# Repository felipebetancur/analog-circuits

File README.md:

# analog-circuits
Various eagle files for analog synths

# Setup
* Add repo to eagle projects directory list, e.g., $HOME/workspace/analog-circuits
* Clone MTIID eagle library
* Add MTIID eagle library to library directory list, e.g., $HOME/workspace/mtiid-eagle-library

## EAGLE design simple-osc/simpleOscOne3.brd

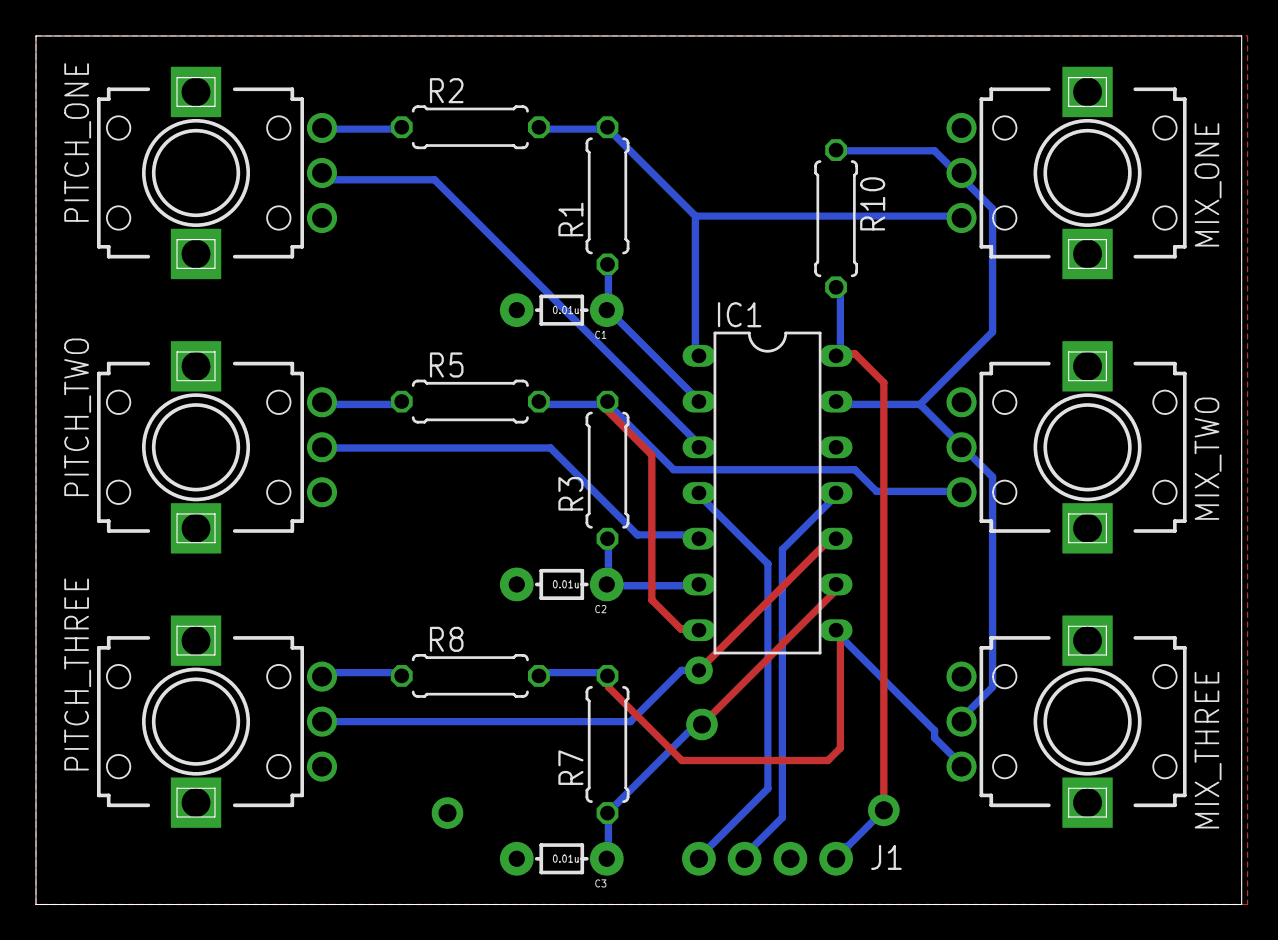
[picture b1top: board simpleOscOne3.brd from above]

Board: 2 copper layers, 67.0 x 48.2 mm, 19 parts (0 on the bottom side), 17 nets.

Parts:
C1, C2, C3: 0.01u; AXIAL-5MM
FRAME1: FRAME-LETTERNO_PACKAGE; DUMMY
IC1: TL084P; DIL14
J1: 1X04_NO_SILK_ALL_ROUND
MIX_ONE: US-EVUF2A; EVUF
MIX_THREE: US-EVUF2A; EVUF
MIX_TWO: US-EVUF2A; EVUF
PITCH_ONE: US-EVUF2A; EVUF
PITCH_THREE: US-EVUF2A; EVUF
PITCH_TWO: US-EVUF2A; EVUF
R1, R2, R3, R5, R7, R8, R10: 10k; 0207/7

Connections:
GND: C1.P$2, C2.P$2, C3.P$2, IC1.12, J1.2, MIX_ONE.1, MIX_THREE.1, MIX_TWO.1, PITCH_ONE.1, PITCH_THREE.1, PITCH_TWO.1
unnamed: PITCH_ONE.3, R2.1
unnamed: IC1.1, MIX_ONE.3, R1.2, R2.2
unnamed: IC1.7, MIX_TWO.3, R3.2, R5.2
unnamed: IC1.3, PITCH_ONE.2
unnamed: C1.P$1, IC1.2, R1.1
unnamed: PITCH_TWO.3, R5.1
unnamed: IC1.5, PITCH_TWO.2
unnamed: C2.P$1, IC1.6, R3.1
unnamed: IC1.8, MIX_THREE.3, R7.2, R8.2
unnamed: PITCH_THREE.3, R8.1
unnamed: IC1.10, PITCH_THREE.2
unnamed: C3.P$1, IC1.9, R7.1
unnamed: IC1.13, MIX_ONE.2, MIX_THREE.2, MIX_TWO.2, R10.1
OUTPUT: IC1.14, J1.1, R10.2
VCC: IC1.4, J1.4
VDD: IC1.11, J1.3

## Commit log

2017-03-09 initial upload of simple oscillator
2017-04-06 creating dir structure for oscillators and sequential circuits
2017-04-06 renaming simple-osc to relaxation-oscillator
2017-04-06 added falstad gif of relaxation oscillator
2017-04-06 adding gif to relaxation oscillator README
2017-04-06 enabled looping for gif
2017-04-06 added inital descritpion for adding eagle libraries and projects

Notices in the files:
parts and their libraries:
SparkFun-Capacitors: Licensing: Creative Commons ShareAlike 4.0 International - https://creativecommons.org/licenses/by-sa/4.0
